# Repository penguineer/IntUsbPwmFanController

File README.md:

# PWM Fan Controller with Internal USB connection

> Controller for PWM-based fans using the internal USB 2.0 header

I have an NVIDIA server GPU which relies on external fans and uses the
`nvidia-smi` cli to report its temperature. In addition, my mainboard
does not allow for fan speed control under
Linux.

As this is my workstation setup and I do not want the fans running at
full speed all the time, I needed a controller to set the fan speed from
software, which easily integrates into my case.

This controller is plugged into an internal USB 2.0 header and offers
the 4-pin PWM header to connect fans.

## License

This work is licensed under
a [Creative Commons Attribution-ShareAlike 4.0 International License](http://creativecommons.org/licenses/by-sa/4.0/).

BY: Stefan Haun (mail at tuxathome.de)

See [LICENSE.txt](LICENSE.txt) for details.

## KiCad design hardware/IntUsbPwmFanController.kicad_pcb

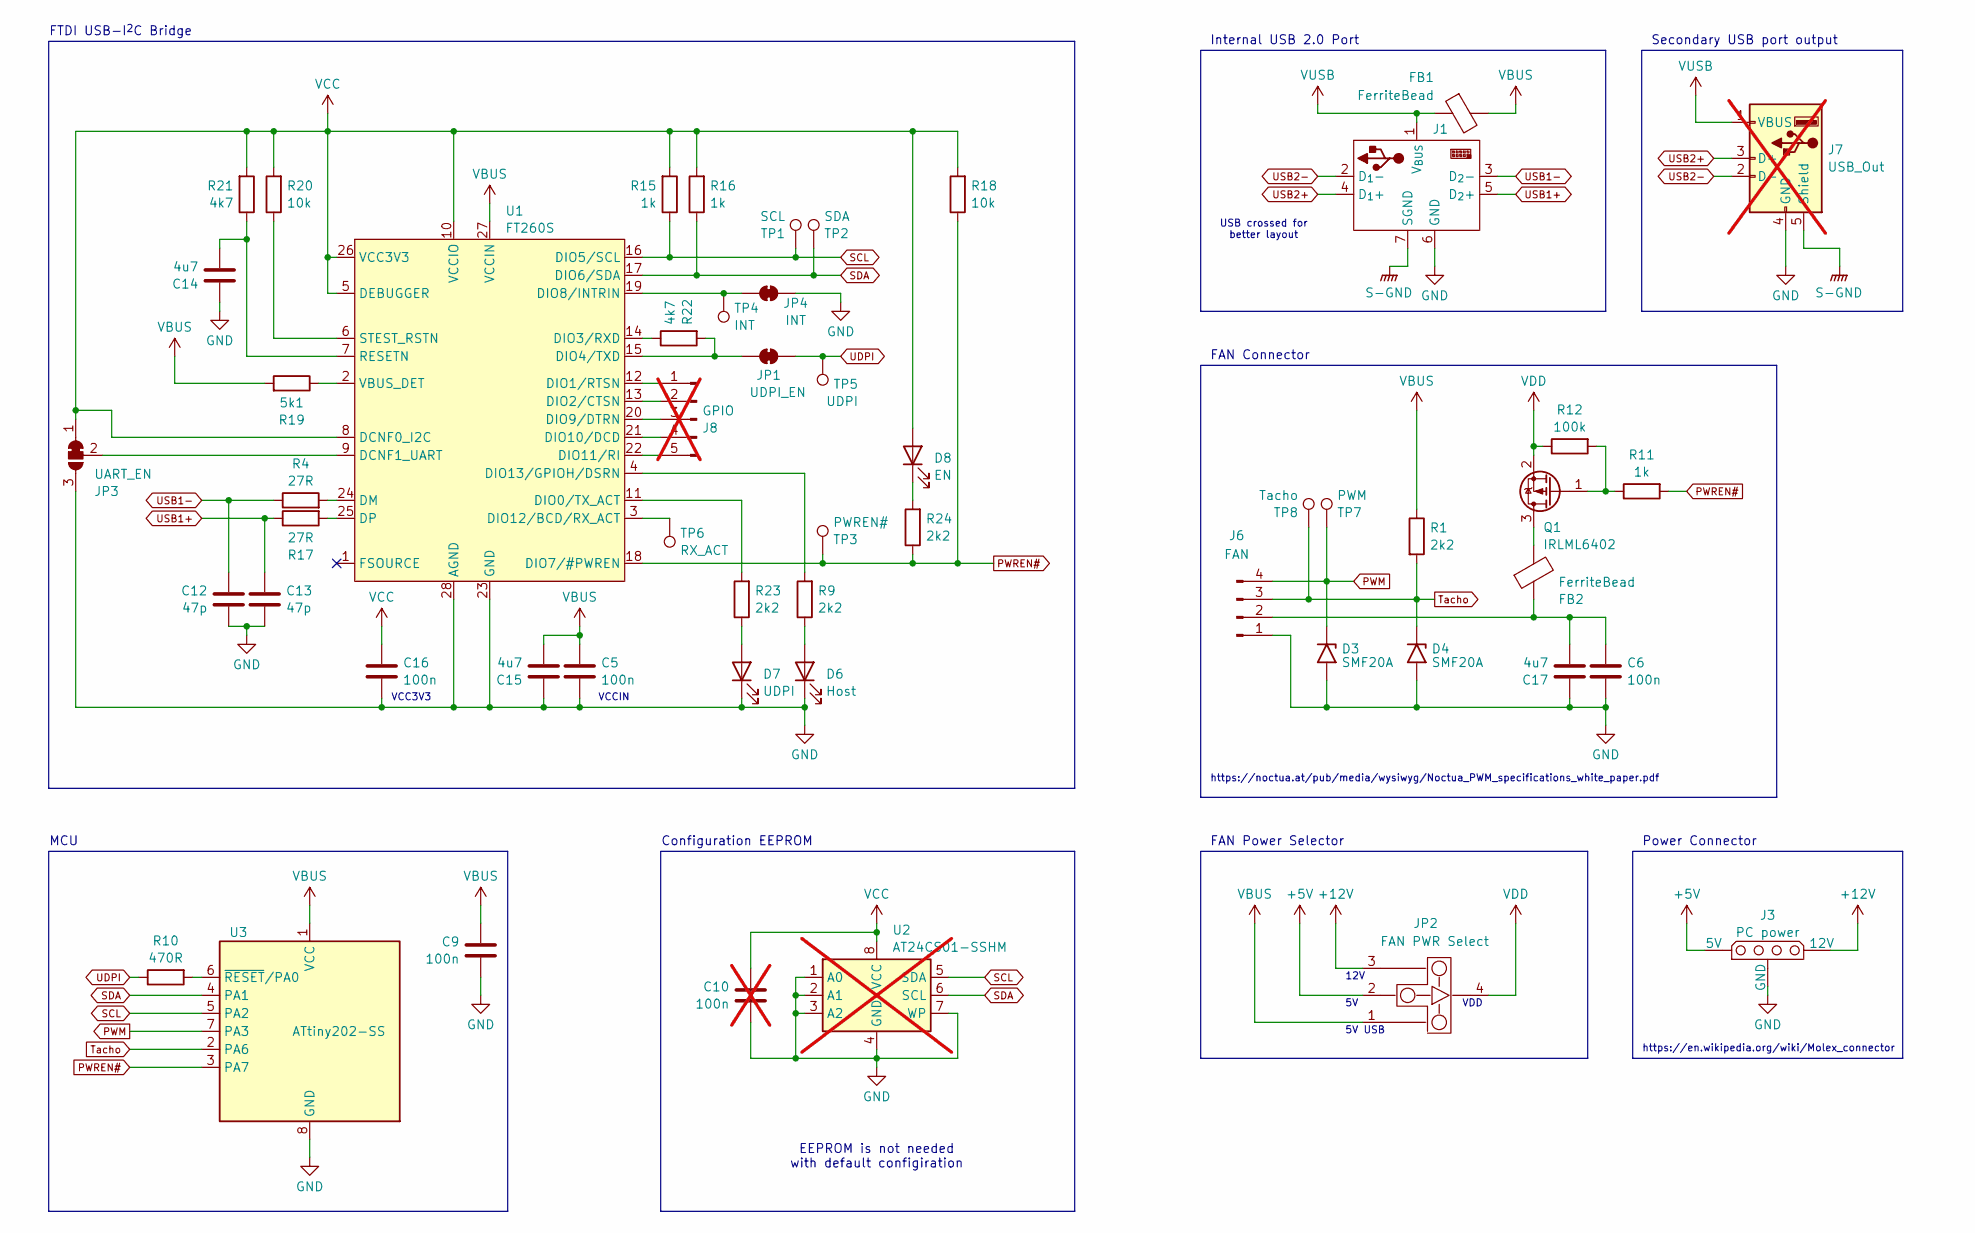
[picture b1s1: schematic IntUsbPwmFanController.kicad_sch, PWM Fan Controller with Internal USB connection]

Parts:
C5, C6, C9, C16: 100n; C_0603_1608Metric_Pad1.08x0.95mm_HandSolder; Mouser No 963-TMK107BJ104MA-T
C10: 100n; C_0603_1608Metric_Pad1.08x0.95mm_HandSolder; Mouser No 963-TMK107BJ104MA-T; not fitted
C12, C13: 47p; C_0603_1608Metric_Pad1.08x0.95mm_HandSolder; Mouser No 80-C0603C470K4HACTU
C14, C15, C17: 4u7; C_0603_1608Metric_Pad1.08x0.95mm_HandSolder; Mouser No 963-TMK107BJ104MA-T
D3, D4: SMF20A; D_SMF; LCSC C151295
D6: Host; LED_0603_1608Metric_Pad1.05x0.95mm_HandSolder; Mouser No 720-LTQ39GQ1S22515
D7: UDPI; LED_0603_1608Metric_Pad1.05x0.95mm_HandSolder; Mouser No 630-HSMC-C130
D8: EN; LED_0603_1608Metric_Pad1.05x0.95mm_HandSolder; Mouser No 720-LTQ39GQ1S22515
FB1, FB2: FerriteBead; R_0603_1608Metric_Pad0.98x0.95mm_HandSolder; Mouser No 81-BLM18SG221TZ1D
J1: Internal USB 2.0 Header Default
J3: PC power; Molex 8981 Vertical
J6: FAN; FanPinHeader_1x04_P2.54mm_Vertical
J7: USB_Out; USB_A_Molex_105057_Vertical; not fitted
J8: GPIO; PinHeader_1x05_P2.54mm_Vertical; not fitted
JP1: UDPI_EN; SolderJumper-2_P1.3mm_Bridged_RoundedPad1.0x1.5mm
JP2: FAN PWR Select; ThreeWayJumper
JP3: UART_EN; SolderJumper-3_P1.3mm_Bridged12_RoundedPad1.0x1.5mm
JP4: INT; SolderJumper-2_P1.3mm_Bridged_RoundedPad1.0x1.5mm
Q1: IRLML6402; SOT-23
R1, R9, R23, R24: 2k2; R_0603_1608Metric_Pad0.98x0.95mm_HandSolder
R4, R17: 27R; R_0603_1608Metric_Pad0.98x0.95mm_HandSolder
R10: 470R; R_0603_1608Metric_Pad0.98x0.95mm_HandSolder
R11, R15, R16: 1k; R_0603_1608Metric_Pad0.98x0.95mm_HandSolder
R12: 100k; R_0603_1608Metric_Pad0.98x0.95mm_HandSolder
R18, R20: 10k; R_0603_1608Metric_Pad0.98x0.95mm_HandSolder
R19: 5k1; R_0603_1608Metric_Pad0.98x0.95mm_HandSolder
R21, R22: 4k7; R_0603_1608Metric_Pad0.98x0.95mm_HandSolder
TP1: SCL; TestPoint_Pad_D1.0mm
TP2: SDA; TestPoint_Pad_D1.0mm
TP3: PWREN#; TestPoint_Pad_D1.0mm
TP4: INT; TestPoint_Pad_D1.0mm
TP5: UDPI; TestPoint_Pad_D1.0mm
TP6: RX_ACT; TestPoint_Pad_D1.0mm
TP7: PWM; TestPoint_Pad_D1.0mm
TP8: Tacho; TestPoint_Pad_D1.0mm
U1: FT260S; TSSOP-28_4.4x9.7mm_P0.65mm
U2: AT24CS01-SSHM; SOIC-8_3.9x4.9mm_P1.27mm; Mouser No 556-AT24CS01-SSHM-T; not fitted
U3: ATtiny202-SS; SOIC-8_3.9x4.9mm_P1.27mm

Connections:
+5V: J3.4 (5V), JP2.2 (OPT2)
+12V: J3.1 (12V), JP2.3 (OPT3)
GND: C5.2, C6.2, C9.2, C10.2, C12.2, C13.2, C14.1, C15.1, C16.2, C17.1, D3.2 (A2), D4.2 (A2), D6.1 (K), D7.1 (K), J1.6 (GND), J3.23 (GND), J6.1, J7.4 (GND), JP3.3 (B), JP4.2 (B), U1.23 (GND), U1.28 (AGND), U2.1 (A0), U2.2 (A1), U2.3 (A2), U2.4 (GND), U2.7 (WP), U3.8 (GND)
unnamed: D6.2 (A), R9.1
unnamed: D7.2 (A), R23.1
unnamed: D8.1 (K), R24.2
unnamed: C6.1, C17.2, FB2.1, J6.2
unnamed: J8.1, U1.12 (DIO1/RTSN)
unnamed: J8.2, U1.13 (DIO2/CTSN)
unnamed: J8.3, U1.20 (DIO9/DTRN)
unnamed: J8.4, U1.21 (DIO10/DCD)
unnamed: J8.5, U1.22 (DIO11/RI)
unnamed: JP1.1 (A), R22.2, U1.15 (DIO4/TXD)
unnamed: JP3.2 (C), U1.9 (DCNF1_UART)
unnamed: JP4.1 (A), TP4.1, U1.19 (DIO8/INTRIN)
unnamed: FB2.2, Q1.3 (D)
unnamed: Q1.1 (G), R11.1, R12.2
unnamed: R23.2, U1.11 (DIO0/TX_ACT)
unnamed: R22.1, U1.14 (DIO3/RXD)
unnamed: TP6.1, U1.3 (DIO12/BCD/RX_ACT)
unnamed: R9.2, U1.4 (DIO13/GPIOH/DSRN)
unnamed: R4.2, U1.24 (DM)
unnamed: R17.2, U1.25 (DP)
unnamed: C14.2, R21.1, U1.7 (RESETN)
unnamed: R20.1, U1.6 (STEST_RSTN)
unnamed: R19.1, U1.2 (VBUS_DET)
unnamed: R10.2, U3.6 (~RESET/PA0)
PWM: D3.1 (A1), J6.4, TP7.1, U3.7 (PA3)
PWREN#: R11.2, R18.1, R24.1, TP3.1, U1.18 (DIO7/#PWREN), U3.3 (PA7)
S-GND: J1.7 (SGND), J7.5 (Shield)
SCL: R15.1, TP1.1, U1.16 (DIO5/SCL), U2.5 (SDA), U3.5 (PA2)
SDA: R16.1, TP2.1, U1.17 (DIO6/SDA), U2.6 (SCL), U3.4 (PA1)
Tacho: D4.1 (A1), J6.3, R1.2, TP8.1, U3.2 (PA6)
UDPI: JP1.2 (B), R10.1, TP5.1
USB1+: C13.1, J1.5 (D_{2}+), R17.1
USB1-: C12.1, J1.3 (D_{2}-), R4.1
USB2+: J1.4 (D_{1}+), J7.3 (D+)
USB2-: J1.2 (D_{1}-), J7.2 (D-)
VBUS: C5.1, C9.1, C15.2, FB1.2, JP2.1 (OPT1), R1.1, R19.2, U1.27 (VCCIN), U3.1 (VCC)
VCC: C10.1, C16.1, D8.2 (A), JP3.1 (A), R15.2, R16.2, R18.2, R20.2, R21.2, U1.5 (DEBUGGER), U1.8 (DCNF0_I2C), U1.10 (VCCIO), U1.26 (VCC3V3), U2.8 (VCC)
VDD: JP2.4 (SEL), Q1.2 (S), R12.1
VUSB: FB1.1, J1.1 (V_{BUS}), J7.1 (VBUS)

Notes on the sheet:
Secondary USB port output
https://en.wikipedia.org/wiki/Molex_connector
Power Connector
USB crossed for better layout
EEPROM is not needed with default configiration
VDD
VCCIN
Internal USB 2.0 Port
5V USB
FAN Connector
12V
MCU
FAN Power Selector
Configuration EEPROM
https://noctua.at/pub/media/wysiwyg/Noctua_PWM_specifications_white_paper.pdf
FTDI USB-I^{2}C Bridge
VCC3V3

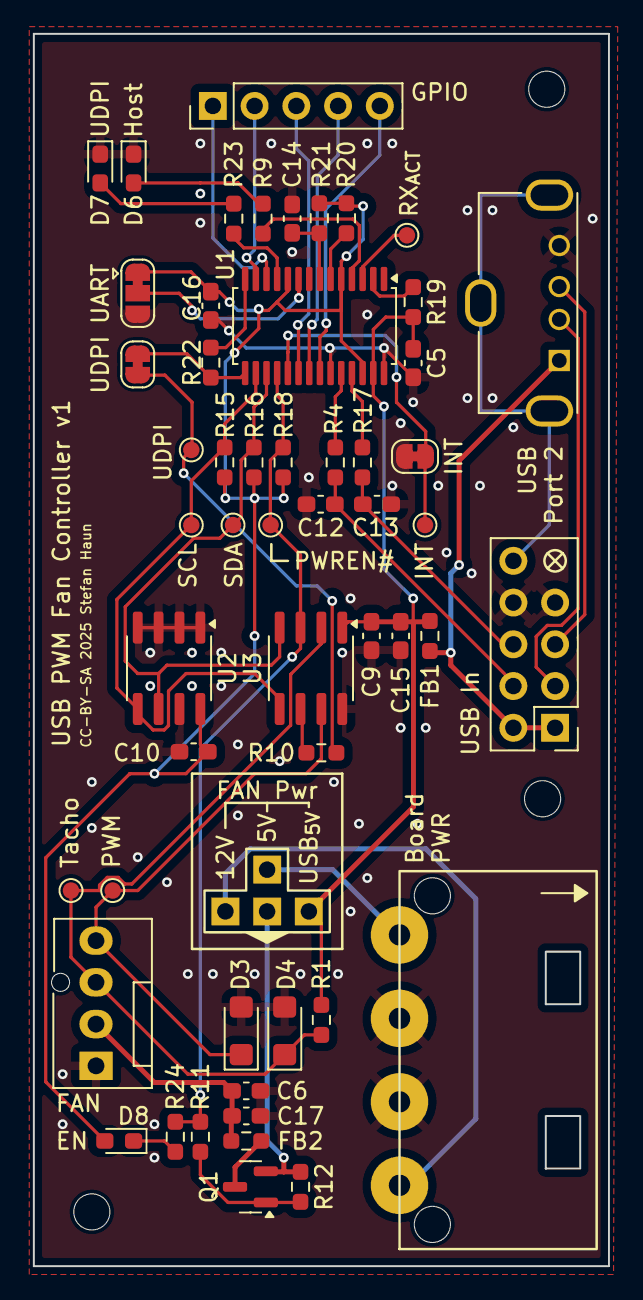
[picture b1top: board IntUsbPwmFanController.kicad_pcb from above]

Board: 2 copper layers, 35.0 x 75.0 mm, 54 parts (0 on the bottom side), 42 nets.

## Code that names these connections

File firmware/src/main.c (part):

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/***** Global variables *****/

uint8_t pwm_target = 0; // Target PWM value
uint16_t tacho_rpm = 0; // Most recent tacho measurement

/***** PWM *****/

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#define PWM_PREBUF ((F_CPU / (8 * 25000)) - 1)

void TCA_init_pwm(void) {
    // Configure PA3 as output
    PORTA.DIRSET = PIN3_bm; // Set PA3 as output

    // TCA0 WO[1] routes to PA3

    // Set TCA0 to single-slope PWM mode
    TCA0.SINGLE.CTRLB = TCA_SINGLE_WGMODE_SINGLESLOPE_gc | TCA_SINGLE_CMP1EN_bm; // Enable WO1 (PA3)

    // Set the period
    TCA0.SINGLE.PER = PWM_PREBUF;
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}

void TCB_init_tacho_counter(void) {
    // Configure PA6 as input
    PORTA.DIRCLR = PIN6_bm; // Set PA6 as input
    PA6_enable_edge_sensing();

    // Configure Event System to route PA6 to TCB0
    EVSYS.ASYNCCH0 = EVSYS_ASYNCCH0_PORTA_PIN6_gc; // Pin PA6
    EVSYS.ASYNCUSER0 = EVSYS_ASYNCUSER0_ASYNCCH0_gc; // route to TCB0

    // Configure TCB0 in event counting mode
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/***** TWI Core *****/

void TWI_slave_init(void) {
    // Configure SCL (PA2) and SDA (PA1) as inputs
    PORTA.DIRCLR = PIN2_bm | PIN1_bm; // leaves other pins unchanged

    // Enable internal pull-ups on SCL (PA2) and SDA (PA1)
    PORTA.PIN2CTRL |= PORT_PULLUPEN_bm;
    PORTA.PIN1CTRL |= PORT_PULLUPEN_bm;

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/***** Sleep Mode *****/

void SLEEP_init(void) {
    // Configure PA7 as input
    PORTA.DIRCLR = PIN7_bm;

    // Enable interrupt on both edges with pull-up
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}

ISR(PORTA_PORT_vect) {
    // ISR(PORTA_PORT_vect) handles interrupts on PA7, which is configured for both edge detection.
    // This ISR is not triggered by PA6, as PA6 is configured for event routing via the Event System
    // and does not generate pin interrupts.

    if (PORTA.INTFLAGS & PIN7_bm) {
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
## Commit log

2025-04-19 Add an editorconfig file
    https://EditorConfig.org
2025-04-19 Add FUNDING information
2025-04-19 Add gitignore for KiCad project
2025-04-19 First draft of the schematic
2025-04-20 Add .gitignore for the firmware
2025-04-20 Add LICENSE and preliminary README for the firmware
2025-04-20 Add a skeleton platform.io project for the firmware
2025-04-20 Add a draft implementation of TWI handling
2025-04-20 Add a draft implementation of PWM
2025-04-20 Add a draft implementation of tacho measurement
2025-04-20 Change how tacho measurement is disabled to avoid unintended ISR calls
2025-04-20 Fix data length calculation for the receive buffer
2025-04-20 Re-assign MCU pins after firmware considerations
2025-04-20 Minor fixes to the code
2025-04-20 Add API and Architecture documentation
2025-04-20 Add a draft implementation of sleep mode
2025-04-21 Add a symbol for the FT260S
2025-04-21 Replace FT201XS (I2C slave) with FT260S (I2C master)
2025-04-21 Invert SLEEP signal interpretation for PWREN#
    Instead of SLEEP, the signal PWREN# is now provided, which is inverted.
2025-04-21 Add (optional) configuration EEPROM
    Since it has a very small footprint and optinal GPIO headers are also
    available, add a configuration EEPROM to the design.
2025-04-21 Fix the solder jumpers
2025-04-21 Add Symbol and Footprint for the 3-way jumper selection
2025-04-21 Use new symbol for the 3-way jumper
2025-04-21 Improve fan connector filtering
2025-04-21 Fix FT260S decoupling cap assignment
    C16 was accidentally assigned to vbus, when it should have been VCC3V3.
2025-04-21 Add symbol and footprint for Molex 8981 Power Connector
2025-04-21 Use the correct Molex connector symbol/footprint
2025-04-21 Add symbol/footprint for the USB 2.0 header
2025-04-21 Use correct symbol/footprint for the USB 2.0 header
2025-04-23 Add a PCB layout draft
2025-04-23 Rename USB 2.0 header to NUC variant
2025-04-23 Add a footprint for an internal USB 2.0 socket
2025-04-23 Change default USB 2.0 header footprint to default socket
2025-04-23 Adjust schematic and PCB to the new footprint
2025-05-03 Add a pinheader USB 2.0 connector
2025-05-03 Switch to a pinheader for the USB connector
2025-06-13 Add Labels and CC to PCB

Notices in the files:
hardware/IntUsbPwmFanController.kicad_pcb:
CC-BY-SA 2025 Stefan Haun
